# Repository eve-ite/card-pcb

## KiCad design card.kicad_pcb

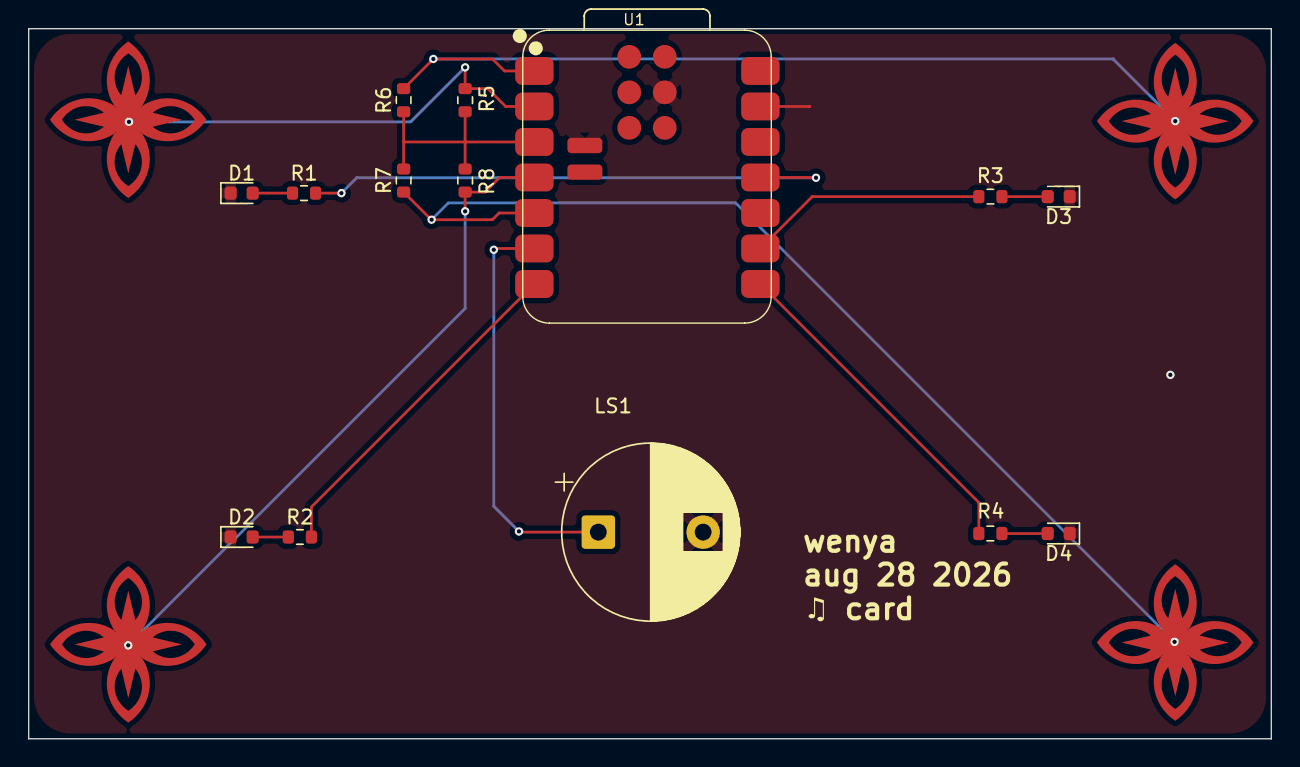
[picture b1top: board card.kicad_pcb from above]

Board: 2 copper layers, 88.9 x 50.8 mm, 18 parts (0 on the bottom side), 15 nets.

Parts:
D1, D2, D3, D4: LED; LED_0603_1608Metric
LS1: Speaker; CP_Radial_D12.5mm_P7.50mm
R1, R2, R3, R4: 1k; R_0603_1608Metric
R5, R6, R7, R8: 1M; R_0603_1608Metric
TP1, TP2, TP3, TP4: TestPoint; flower
U1: XIAO-ESP32-C3-SMD

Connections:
GND: D1.1 (K), D2.1 (K), D3.1 (K), D4.1 (K), LS1.2, U1.13 (GND), U1.18 (GND), U1.22 (GND)
LED1: R1.2, U1.11 (D10)
LED2: R2.2, U1.7 (D6)
LED3: R3.2, U1.9 (D8)
LED4: R4.2, U1.8 (D7)
unnamed: D1.2 (A), R1.1
unnamed: D2.2 (A), R2.1
unnamed: D3.2 (A), R3.1
unnamed: D4.2 (A), R4.1
unnamed: R6.2, TP1.2 (1_1), U1.1 (D0)
unnamed: R5.1, TP2.2 (1_1), U1.2 (D1)
unnamed: R5.2, R6.1, R7.2, R8.2, U1.3 (D2)
unnamed: R8.1, TP3.2 (1_1), U1.4 (D3)
unnamed: R7.1, TP4.2 (1_1), U1.5 (D4)
unnamed: LS1.1, U1.6 (D5)
